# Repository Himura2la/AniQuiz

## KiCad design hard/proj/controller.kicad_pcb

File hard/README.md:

[Made with KiCAD](http://kicad-pcb.org/)
==========

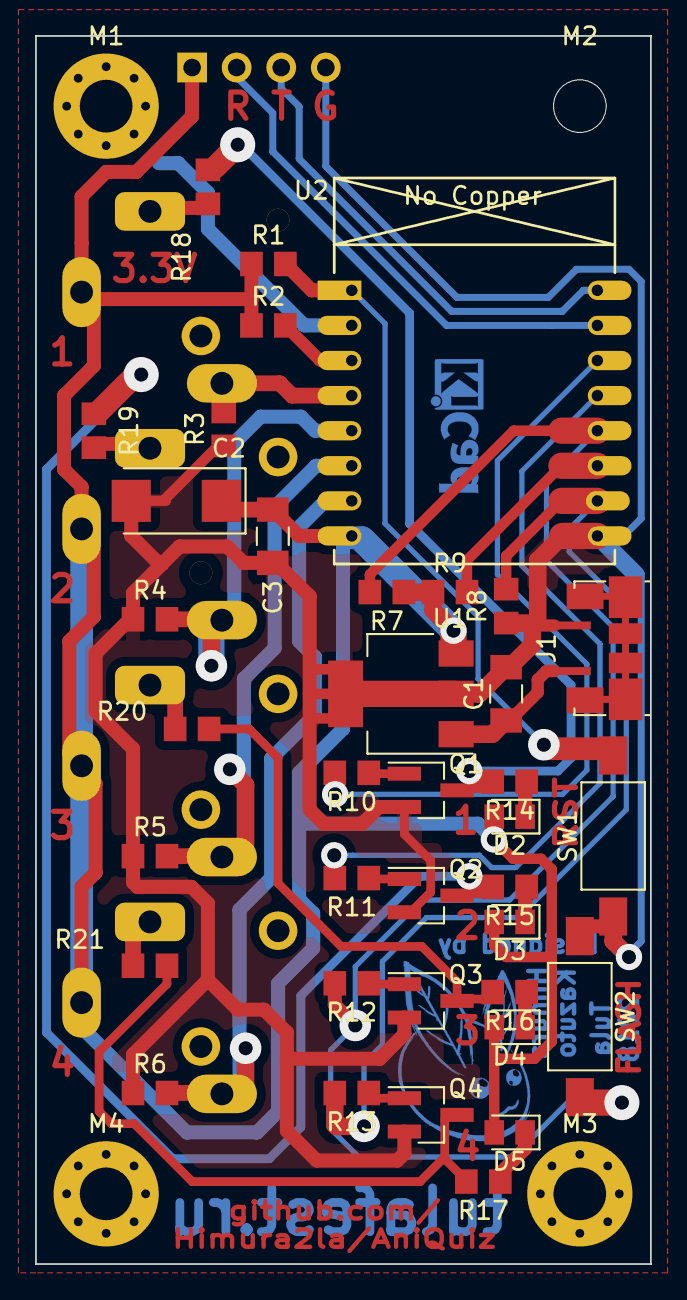
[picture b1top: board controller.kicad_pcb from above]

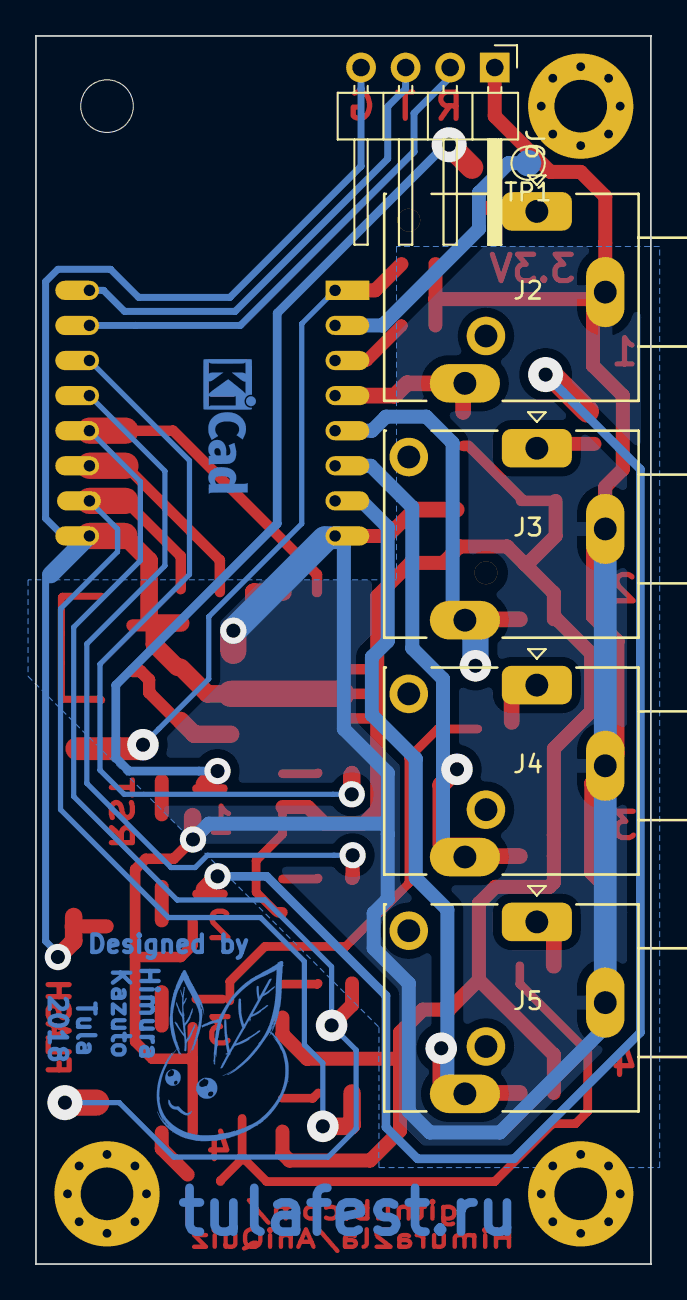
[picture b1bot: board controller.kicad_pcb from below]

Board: 2 copper layers, 35.0 x 70.0 mm, 47 parts (6 on the bottom side), 33 nets.

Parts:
C1: 0.47uF; C_1206_3216Metric_Pad1.39x1.80mm_HandSolder
C2: 33uF; CP_EIA-6032-28_Kemet-C_Pad2.24x2.40mm_HandSolder
C3: 0.1uF; C_1206_3216Metric_Pad1.39x1.80mm_HandSolder
D2: LED1; LED_0805_2012Metric_Pad1.12x1.40mm_HandSolder
D3: LED2; LED_0805_2012Metric_Pad1.12x1.40mm_HandSolder
D4: LED3; LED_0805_2012Metric_Pad1.12x1.40mm_HandSolder
D5: LED4; LED_0805_2012Metric_Pad1.12x1.40mm_HandSolder
J1: microUSB; USB_Micro-B_Molex_47346-0001
J2: EXT1; StereoJack_3.5mm_Switch_Ledino_KB3SPRS_Horizontal
J3: EXT2; StereoJack_3.5mm_Switch_Ledino_KB3SPRS_Horizontal
J4: EXT3; StereoJack_3.5mm_Switch_Ledino_KB3SPRS_Horizontal
J5: EXT4; StereoJack_3.5mm_Switch_Ledino_KB3SPRS_Horizontal
J6: UART; PinHeader_1x04_P2.54mm_Horizontal
M1, M3, M4: MountingHole_3mm_Pad_Via
M2: MountingHole_3mm
Q1, Q2, Q3, Q4: BC848B; SOT-23_Handsoldering
R1, R2, R3, R4, R5, R6, R7, R8, R9, R10, R11, R12, R13: 10k; R_0805_2012Metric_Pad1.29x1.40mm_HandSolder
R14, R15, R16, R17, R18, R19, R20, R21: 180; R_0805_2012Metric_Pad1.29x1.40mm_HandSolder
SW1: RESET; SW_SPST_FSMSM
SW2: FLASH; SW_SPST_FSMSM
TP1: ADC; TestPoint_Pad_D1.5mm
U1: LM3940; SOT-223-3_TabPin2
U2: ESP-07v2

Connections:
+3V3: C2.1, C3.1, D2.2, D3.2, D4.2, D5.2, J2.S, J3.S, J4.S, J5.S, J6.1, R1.1, R2.1, R7.1, R9.1, U1.3, U2.8
/5V: C1.1, J1.1, U1.1
/ADC: TP1.1, U2.2
/BTN1: J2.R, R3.2, U2.4
/BTN2: J3.R, R4.2, U2.5
/BTN3: J4.R, R5.2, U2.6
/BTN4: J5.R, R6.2, U2.7
/CHIP_EN: R2.2, U2.3
/LED1_CTL: R10.2, U2.14
/LED1_PWR: Q1.3, R14.2, R18.2
/LED2_CTL: R11.2, U2.13
/LED2_PWR: Q2.3, R15.2, R19.2
/LED3_CTL: R7.2, R12.2, SW2.2, U2.12
/LED3_PWR: Q3.3, R16.2, R20.2
/LED4_CTL: R8.2, R13.2, U2.10
/LED4_PWR: Q4.3, R17.2, R21.2
/RESET: R1.2, SW1.2, U2.1
/STATUS_LED: R9.2, U2.11
/UART_RX: J6.2, U2.15
/UART_TX: J6.3, U2.16
/XLED1: J2.T, R18.1
/XLED2: J3.T, R19.1
/XLED3: J4.T, R20.1
/XLED4: J5.T, R21.1
GND: C1.2, C2.2, C3.2, J1.5, J6.4, Q1.2, Q2.2, Q3.2, Q4.2, R3.1, R4.1, R5.1, R6.1, R8.1, SW1.1, SW2.1, U1.2, U2.9
unnamed: D2.1, R14.1
unnamed: D3.1, R15.1
unnamed: D4.1, R16.1
unnamed: D5.1, R17.1
unnamed: Q1.1, R10.1
unnamed: Q2.1, R11.1
unnamed: Q3.1, R12.1
unnamed: Q4.1, R13.1

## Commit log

2018-05-20 first tries
2018-05-20 cleaning
2018-05-20 game-config
2018-05-20 'board'
2018-05-20 board started
2018-05-20 helmet to header
2018-05-20 readme
2018-05-20 drop tests and icons
2018-05-27 saga added
2018-05-27 timer!
2018-05-27 refactoring
2018-05-27 fixed timers sync
2018-05-27 MQTT Sending
2018-05-30 hardware enter
2018-05-30 fix lib
2018-05-30 transistors
2018-05-30 need to draw jack
2018-05-31 schema done
2018-05-31 testpin
2018-05-31 pcb started
2018-05-31 some PCB
2018-06-02 Commands via HTTP
2018-06-02 server
2018-06-02 x-url parsing
2018-06-02 hardware connection is almost done
2018-06-03 ready to route
2018-06-03 small fix
2018-06-03 routed
2018-06-04 fixing PCB
2018-06-06 working
2018-06-06 lib installer
2018-06-07 PCB graphics
2018-06-07 fix DRC
2018-06-07 lib init rework
2018-06-07 small fixes
2018-06-07 edge filling
2018-06-10 export
2018-06-21 move to KiCad 5 + deleted PCB
2018-06-21 restarted sch
2018-06-21 layouted
2018-06-22 routing
2018-06-24 zones+symbols
2018-06-24 errors (((
2018-06-28 fixing errors
2018-06-30 firmware started
2018-07-01 small improvements
2018-07-01 fixing
2018-07-06 finalization
2018-07-08 fixing error in regulator
2018-07-08 esp connected
2018-07-08 wifi connection improved
2018-07-23 reSolve 0.13.1
